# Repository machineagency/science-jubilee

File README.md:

# 🔬🧪 Science Jubilee ⚡⚙️
### Controlling Jubilees for Science!

<!--  -->

<!---  --->

<!--  -->

> Use an open-source toolchanger to do science

This repository hosts files to build and control a [Jubilee](https://jubilee3d.com/index.php?title=Main_Page) for scientific applications. The core of the software is a Python interface for Jubilee to navigate labware installed in the machine. We currently provide assembly instructions, control software, and examples for various tools including OT-2 pipettes, syringes, and cameras. While these tools might cater exactly to your planned use case, they most likely will not! We share these files as a starting point rather than an endpoint: we also provide instructions for developing new tools and associated software for controlling them. We hope you will build new tools for your application and contribute them back to the community for others to use and extend 🛠️

_Check out the [Documentation](https://science-jubilee.readthedocs.io/en/latest/index.html) to get started!_

## Overview
### Hardware
This repository is designed to be used with the Jubilee platform, outfitted with tools for laboratory automation. Jubilee an open-source & extensible multi-tool motion platform—if that doesn't mean much to you, you can think of it as a 3D printer that can change its tools. You can read about [Jubilee](https://jubilee3d.com/index.php?title=Main_Page) more generally at the project page.

### Software
The software here is intended to control Jubilee from Python scripts or Jupyter notebooks to design and run experiments. The folders are organized as follows:
```
calibration/                 # notebooks to support machine & tool setup/calibration
tool_library/                # design files, assembly instructions, & configuration info for all tools & plates
src/
└── science_jubilee/
    ├── Machine.py               # jubilee machine driver
    ├── tools/
    │   ├── configs/             # all tool configs are here
    │   ├── Tool.py              # base tool class
    │   └── ...                  # all tool modules are here
    ├── decks/
    │   ├── configs/             # all deck configs are here
    │   ├── Deck.py              # base deck class
    │   └── ...                  # all deck modules are here
    └── labware/
        ├── labware_definitions/ # all labware definitions are here
        └── Labware.py           # base labware class
```

### Labware and Wetware
The basic functionality supported by this software is intended to be used with a custom deck which accommodates up to 6 standard sized microplates.

### Using science_jubilee
You can import and use `science_jubilee` modules by importing the modules you need at the top of your python file/notebook. For example, if we want to pipette using a lab automation deck, we might write:
```python
from science_jubilee.Machine import Machine                             # import machine driver
from science_jubilee.decks.LabAutomationDeck import LabAutomationDeck   # import lab automation deck module
from science_jubilee.tools.Pipette import Pipette                       # import pipette module
...                                                                     # you can import other decks/tools here, or make your own!
```
We can then make use of these modules in our code:
```python
m = Machine()                                                  # connect to your jubilee
deck = m.load_deck(deck_config_name)                           # setup your deck
tip_rack = deck.load_labware(opentrons_96_tiprack_300ul, 0)    # install an opentrons tip rack in slot 0 of the deck
pipette = Pipette(<index>, <name>, <tip_rack>, <config_file>)  # instantiate your pipette tool
m.load_tool(pipette)                                           # configure the pipette for use on the machine
...
```

<!-- pyscaffold-notes -->

## Note

This project has been set up using PyScaffold 4.5. For details and usage
information on PyScaffold see https://pyscaffold.org/.

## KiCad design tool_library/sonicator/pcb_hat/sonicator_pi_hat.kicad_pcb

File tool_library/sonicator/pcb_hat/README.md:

Note: see [machineagency/sonication_station](https://github.com/machineagency/sonication_station) for more details for this solution.

# Sonicator PCB

This PCB attaches on top of the Raspberry Pi enabling its GPIOs to control the Sonicator.

## Fabrication

To make this pcb, you'll need to send files (usually gerbers) out to a PCB Fab house of your choice.
Here are some options:

* [OSH Park](https://oshpark.com/) will actually natively accept **.kicad\_pcb** files directly. (This is probably the easiest option.)
    * [instructions for gerber generation](https://docs.oshpark.com/design-tools/kicad/generating-kicad-gerbers/)
* [PCBWay](http://pcbway.com/)
    * [instructions for gerber generation](https://www.pcbway.com/blog/help_center/Generate_Gerber_file_from_Kicad.html)
* Bay Area Circuits has a No-Silk-No-Soldermask 24-hour [Bare Bones Special](https://bayareacircuits.com/prototype-printed-circuit-boards-pcbs/) for time crunched prototypes.

## Assembly

This PCB can be assembled by hand with some tweezers, a microscope (or cheap microscope webcam), and, optionally, a stencil.
Parts will need to be ordered from the BOM.
(You can regenerate the BOM from the native Kicad files.)

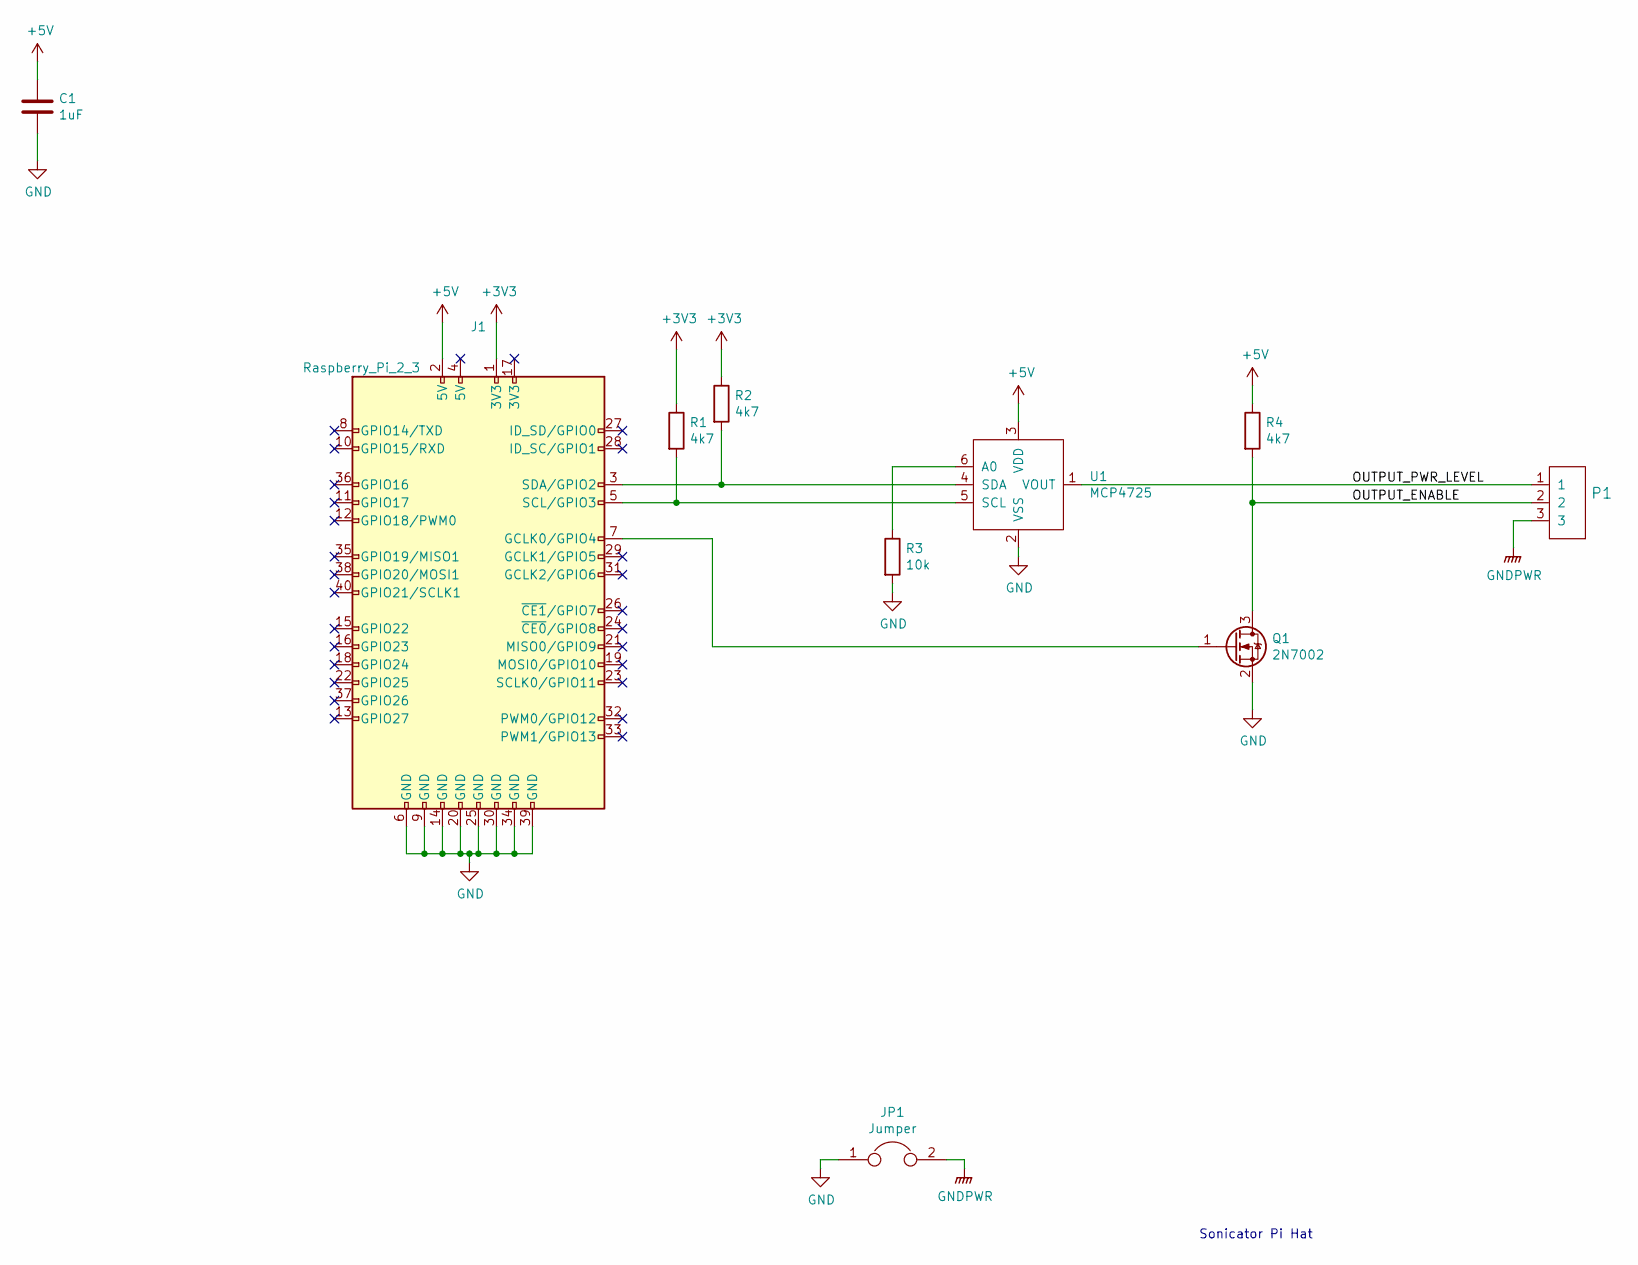
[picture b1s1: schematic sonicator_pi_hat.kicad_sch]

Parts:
C1: 1uF; C_0603_1608Metric
J1: Raspberry_Pi_2_3; PinHeader_2x20_P2.54mm_Vertical
JP1: Jumper; SolderJumper-2_P1.3mm_Bridged_Pad1.0x1.5mm
P1: 3pos_terminal_block; TerminalBlock_Phoenix_MPT-0,5-3-2.54_1x03_P2.54mm_Horizontal
Q1: 2N7002; SOT-23
R1, R2, R4: 4k7; R_0603_1608Metric_Pad1.05x0.95mm_HandSolder
R3: 10k; R_0603_1608Metric_Pad1.05x0.95mm_HandSolder
U1: MCP4725; TSOP-6_1.65x3.05mm_P0.95mm

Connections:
+3V3: J1.1 (3V3), R1.1, R2.1
+5V: C1.1, J1.2 (5V), R4.1, U1.3 (VDD)
/OUTPUT_ENABLE: P1.2, Q1.3 (D), R4.2
/OUTPUT_PWR_LEVEL: P1.1, U1.1 (VOUT)
GND: C1.2, J1.6 (GND), J1.9 (GND), J1.14 (GND), J1.20 (GND), J1.25 (GND), J1.30 (GND), J1.34 (GND), J1.39 (GND), JP1.1, Q1.2 (S), R3.2, U1.2 (VSS)
GNDPWR: JP1.2, P1.3
unnamed: J1.3 (SDA/GPIO2), R2.2, U1.4 (SDA)
unnamed: J1.5 (SCL/GPIO3), R1.2, U1.5 (SCL)
unnamed: J1.7 (GCLK0/GPIO4), Q1.1 (G)
unnamed: R3.1, U1.6 (A0)

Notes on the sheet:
Sonicator Pi Hat

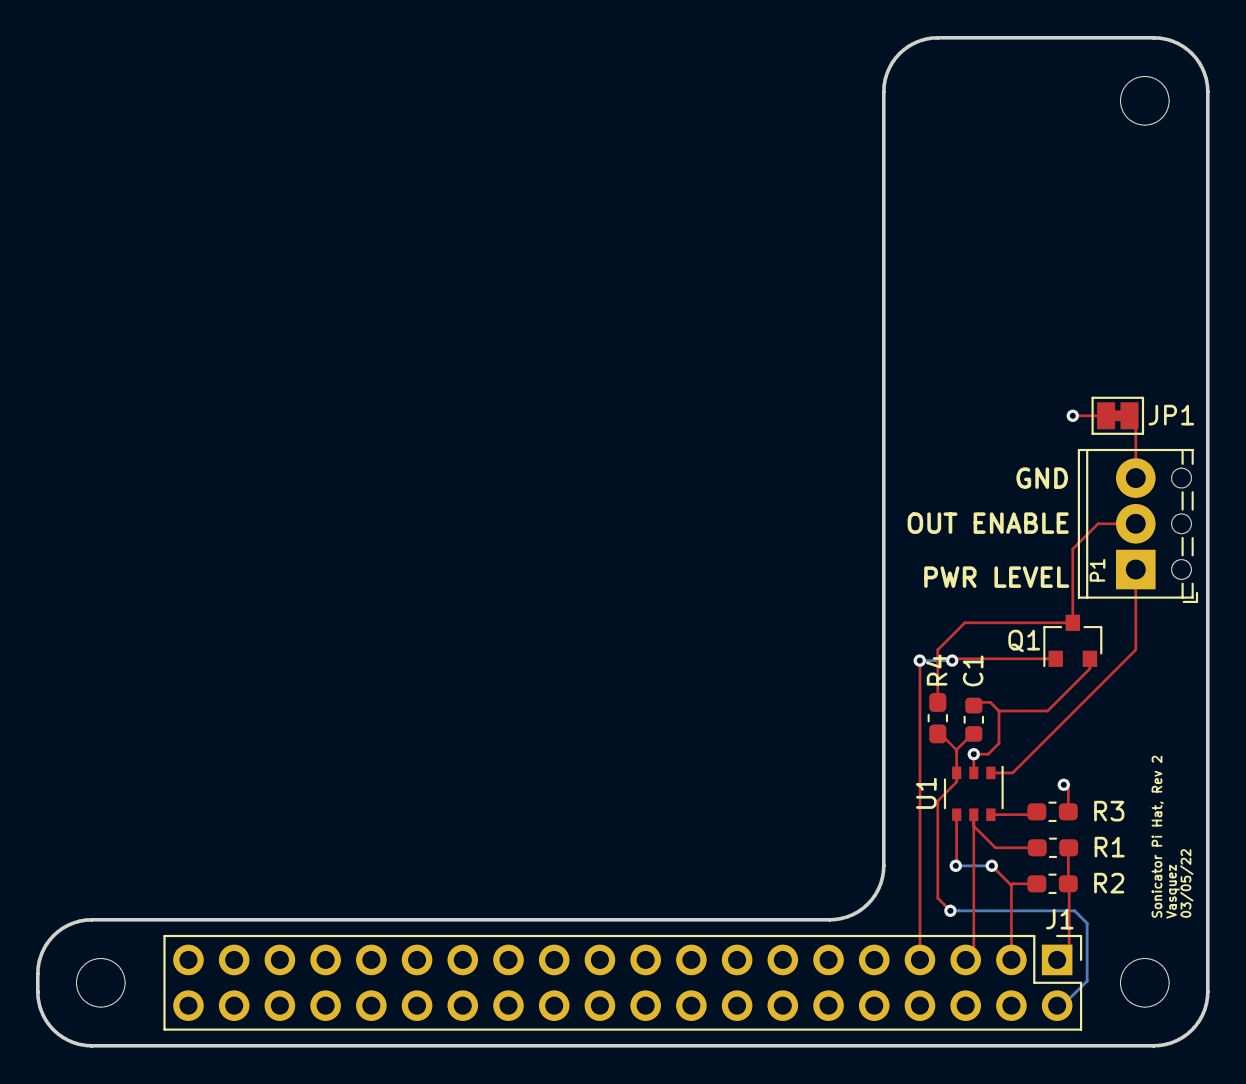
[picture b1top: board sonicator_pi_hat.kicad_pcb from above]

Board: 2 copper layers, 65.0 x 56.0 mm, 10 parts (0 on the bottom side), 10 nets.

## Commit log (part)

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2024-01-26 Updated and fixed setup.py file as installation on Windwows/Mac OS systems
2024-01-26 Fixed module imports and removed unused ones. Added `tool_offset` to :class:`Tool` and removed attribute from Pipette and Webcamera tools
2024-01-26 Fixed config files for deck and WebCamera
2024-01-30 Added method for 3-point manual offset applied to labware once loaded onto deck- better allignment between deck and carriage arm
2024-01-31 Initial commit for Spectrometer Tool
2024-02-01 Included save option for method and finalized metadata and filename options. Still need to run final testing on functions
2024-02-01 Added documentation and .stl files for WebCamera tool
2024-02-01 Updated the documentation Labware notebook with new manual_offset() method example
2024-02-16 Updated OT2 pipettor documentation and consolidated design files into single folder
2024-02-21 fixed issue with well ordering
2024-02-21 Fixed device usb initialization and light source connection
2024-02-27 made tuple lowercase so tuple loctions handled correctly in _get_xyz
2024-02-27 Added `current_well` attribute to Pipette Tool
2024-02-28 add default safe_z for use without Deck installed
2024-02-28 add MA labware & deck
2024-02-29 add tool parking post notebook
2024-02-29 add XY alignment notebook
2024-03-14 Added `well.has_tip` for tip tracking strategy and `well.labware_name` for better well object display when called
2024-03-19 Expanded `manula_offset` for better functionalities and added `clean_tip` attribute to Well class for Tip Tracking strategy
2024-03-19 Removed unused attribute `first_available_tip` as implementing new TipTracker class
2024-03-20 Added new labware and fixed deck corner location
2024-03-25 Fixed type isse in Labware.manual_offset()
2024-03-25 Added focus length parameter for WebCamera tool
2024-03-25 Fixed post_laod method for Pipette to prime it for ready to use
2024-03-25 Fixed missing return statement
2024-03-25 cahnge tip_overlap as different from OT2 robot
2024-03-26 added small delay for autofocus
2024-03-26 fixed data type for mixing if Location is given instead of Well
2024-03-26 Changed variable name and changed default value for load_manualOffset
2024-04-01 fix standalone check
2024-04-02 Increase timeout default value for WebCamera connection
2024-04-02 fixed manual_offset with correct point translation
2024-04-02 pass over unocfigured tool numbers
2024-04-02 Included additional parameter for sonicator cleaning protocol
2024-04-02 update parking tool position calibration notebook
2024-04-09 docs update: images for tool builds
2024-04-13 add syringe extruder tool
2024-04-17 gel printing test nb
2024-04-19 Scaled up OT Pipette guide rails for correct tool position on post and consolidaetd into single file
2024-04-19 Updaetd blowout and mix speed and lowered pipette return_tip height for better physical tip handling
2024-04-19 Fixed module import. Cleaned out lamp on/off logic. Updated MeasurementManager and included read_from_file method in tool
2024-04-21 finalize calibration notebook for parking position
2024-04-22 add G10 command to machine, update gel printing nb
2024-04-22 syringe printing updates
2024-04-23 gel printing updates
2024-04-23 add cleaned gel extrusion nb
2024-04-23 Update Camera.py
    edit path for cam calibration file
2024-04-25 Add updated OT assembly instructions
    changed tool wing screw length. everything else is the same.
2024-04-26 Update conf.py with edit in github functionality
2024-04-27 switch to markdown
2024-04-27 Update Makefile
2024-04-27 mv and renames
2024-04-27 updated notebook for pipette and camera tools, as well as Labware object
2024-04-27 Move file to the proper location
2024-04-27 minimum working afl piston code
2024-04-28 pre-commit
2024-04-28 fix links, add labels
2024-05-03 Rename .readthedocs.yml to .readthedocs.yaml
2024-05-08 made config and default edits for setup for demo in slovenia. Changed default speed for all moves in Machine.py and added a 0.5s sleep after aspirating to pipette, these changes are probably worth mo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
2024-05-08 add colormix wiring pdf
2024-05-08 add config.g file for functional color mixing demo
2024-05-09 update doc links
2024-05-10 replaced by ci.yml
2024-05-10 rm last edited
2024-05-10 Create color_mixing_setup.md
    https: //github.com/machineagency/science_jubilee/commit/8e75836e9eeb0b5e8f271ce2b2f13d4bed2bb60a
2024-05-10 placeholder
2024-05-10 science-jubilee
2024-05-10 precommit
    @bsubbaraman the rest of the precommit warnings/errors can wait. I'll be sure to address these soon
2024-05-13 hack on web camera focus offset
2024-05-13 update docs website to science-jubilee
2024-05-13 _ to - and xrefs
2024-05-13 edit in github
2024-05-13 toctree
2024-05-13 just ubuntu
2024-05-13 comment coverage for now
2024-05-13 fix relative link
2024-05-13 forgot to comment some coverage lines
2024-05-13 Hide toctree
2024-05-14 extra testing deps
2024-05-14 add :hidden: to toctree and add rst grid
2024-05-14 fix figures
2024-05-14 video formatting
2024-05-17 spurious toctree element
2024-05-23 Update OT2_Pipette_Configuration.md
    Minor spelling fixes
2024-05-23 assembly instructions link
2024-05-23 add 3d printed only endstop
    https://discord.com/channels/1116423666905915452/1116435802923204759/1243296567130067036
2024-05-27 avoid 100 MB limit
2024-05-27 Merge pull request #110 from machineagency/sterling
    spurious toctree element
2024-05-28 Update config.yml allow blank issues
2024-05-29 split deps to optionals and environment.yml
    need to verify that imports can still work (i.e., files are separated in a way that import errors won't get thrown when trying to use e.g., non-camera functions)
2024-06-07 start intro guide
2024-06-07 add example config files
2024-06-07 edits to new developer guide
2024-06-12 Fix links and add details to deck build guide
2024-06-12 add to new developer guide
2024-06-13 fix broken jubilee discord link
2024-06-13 add new section on labware calibration
2024-06-13 add new user guide to getting started page
2024-06-13 finish edits on new user guide
2024-06-13 remove config gcode files from PR
2024-06-13 remove trailing whitespace
2024-06-13 add newlines
2024-06-13 formatting?
2024-06-14 use `precommit run --all-files`
2024-06-14 hardware, tools, merge into index, toctree
2024-06-14 Science Jubilee instead of Jubilee
2024-06-14 update tools based on filastruder feedback
    https://discord.com/channels/627982902738681876/755173997305659402/1251195387314835668
    https://discord.com/channels/627982902738681876/755173997305659402/1251195444613349457
2024-06-18 add page titles for build instructions
2024-06-18 add youtube videos (using sphinx-contrib-youtube)
2024-06-27 put correct link in readme
2024-07-01 add clarification on carnet departure
2024-07-08 Trigger Build
2024-07-08 images
2024-07-08 custom tools
2024-07-08 mute last video
2024-07-08 rm separate tool prereq file
2024-07-12 add HTTPsyringe tool to interact with digital pipette over HTTP
2024-07-16 bug fixes to syringe tool
2024-07-18 modify HTTPsyringe to support multiple syringe tools
2024-07-23 stash changes
2024-07-30 Update jubilee_travel.md with dimensions and products
2024-07-30 Update jubilee_travel.md add cardboard box links
2024-08-15 add speed control to digital syringe tool
2024-08-15 add wiper to mix
2024-08-20 remove references to abondoned ds3502 potentiometer control
2024-08-20 add speed control to syringe tool access
2024-08-21 add intro to pipette tool
2024-08-21 add recommended upgrades to parts list
2024-08-21 local updates
2024-08-22 add call-out about attaching limit switch to assembly docs
2024-08-22 overhaul of pipette docs and outline new additions for procedure documentation
2024-08-22 more formatting
2024-08-22 format
2024-08-22 white space
2024-08-22 fix format;
2024-08-22 add new parking post positioning documentation
2024-08-22 pre commit fix
2024-08-26 debug syringe tool
2024-08-28 stash toffsets draft
2024-08-30 initial rearrangement of bed plate docs
2024-09-02 add logging for HTTP requests to Duet board
2024-10-10 Add documentation on tool ball sensor crash detection
2024-10-10 typos
2024-10-14 fix formatting
2024-10-14 add initial logic to handle crash detected messages from jubilee
2024-10-17 add rotation direction check to labware offset correction
2024-10-17 fix crash detection code
2024-10-21 format;
2024-10-21 format step files. Cant figure out how to exclude from pre-commit so here we go
2025-01-20 add new labware
2025-01-24 Update OT2_Pipette_Configuration.md
    Correction of typos and formatting
2025-01-24 newline at end of file
2025-01-25 end-of-file-fixer pre-commit
2025-01-25 Update .pre-commit-config.yaml
    rearranging placement of end-of-file-fixer
2025-03-01 Update ci.yml artifact v4
    v3 deprecated
2025-03-05 debugging for AFL integratin
2025-03-11 afl updates
2025-03-11 pre-commit format
2025-03-22 Update pipette_tool.md
    Duplicate section header to section 2. Proposed new section 4 header for setting steps/mm and step type
2025-03-26 add spectral sensor tool
2025-03-26 isort
2025-03-27 add convenience function to list all available labware
2025-03-30 previous config file for the 10cc syringe tool had been overwritten
2025-03-30 add opentrons p1000 tiprack and falcon brand 96 well plate
2025-03-31 add syringe tool changes
2025-04-01 Updated lab automation bed.g file
    Bed should be moved down after mesh bed compensation
2025-04-02 adding deck configuration files
2025-04-03 new webcam tool (usb arducam) for POSE25
2025-04-15 update windows installation instructions
2025-04-18 Do you really need 300 reusable cable ties from amazon?
    Original requests 100+ each of 4" and 8" reusable cable ties.
    Substitute it for a combo pack.
2025-04-23 fix end of file newline
2025-04-23 black formatting
2025-05-20 checkpoint
2025-05-22 syringe tool calibration notebook
2025-05-22 test
2025-05-22 Update ci.yml
    remove testing on 3.8 to debug testing issue
2025-05-28 bad path for windows install
2025-06-03 swap order of REL and toolchanger_carriage instructions in menu
    The pulley assembly must be constructed first before completion of the REL, but instruction sare in this other page.
2025-06-03 Add required prints and alternate instructions for machined z-plates in Lower Frame Assembly
2025-06-03 Specify 3d-parts needed for Aluminum motor plate assembly
2025-06-03 Clarify heatset insert preparation:
    Clarify what parts do not need to be prepared with heat inserts if machined parts were purchased
    Indicate that heat-setting can be done later. This makes it a bit more manageable to print parts as needed.
2025-06-03 Clarify that machined CoreXY Stepper mounts are included in default Filastruder kit—no need to purchase them
2025-06-03 clarify emphasis on **not** printing
2025-06-03 add deck plate for AFL module
2025-06-04 add afl tool stub
2025-06-04 black formatting on labware and HTTPsyringe
2025-06-04 clean up some docs
2025-06-06 add some advice for the initial motor plate assembly
    It's indicated in the diagram, but the significance doesn't become clear until you have to tension the belt (if placed too far away then there is not enough room for tensioning)
2025-06-06 add recommended backup parts list
2025-06-13 typo fix in main build page
2025-06-13 include nylon washers in recommendation
2025-06-13 Include instructions for current Duet 3 Mini + 3 HC
    - clarify how the back panel layout has changed
    - clarify lack of nylon washers in filastruder kit
    - clarify absence of SSR in the absence of heating option
2025-06-13 add 3d-printed parts manifest to z-axis instructions
2025-06-13 add printed part requirements for REL
2025-06-13 include printed part list and assembly comments in toolchanger carriage build
2025-06-13 rant about 3d printing your own parts
2025-06-13 tidy comments in heaset insert installation instructions
2025-06-13 molex crimping is not required background knowledge for filastruder kit
2025-06-14 Add links for printing M2.5 standoffs for mounting RPi
2025-06-14 Add wiring instructions
    - Clean up typos
    - Include instructions & photos on fuse installation
    - Add link to protective cover on terminal box
    - Add smoke-test instruction
2026-02-18 minor change to installation.md
2026-02-26 Update installation.md
    added some extra description about making and selecting kernel
2026-02-27 Add POSE26 demo tools and configs
2026-03-31 reorganize tool configs
2026-03-31 remove unused wiki folder
2026-03-31 add return in tip_check decorator
2026-04-01 unit conversion but in spectrometer.py
2026-04-01 move config finder out of tool modules and fix syringe config loading
2026-04-08 birdseye demo
2026-04-08 reorganize birdseye calibration files
2026-04-21 add connection message
2026-04-21 remove print statement in Machine.py
2026-04-21 rename p1000 config file
